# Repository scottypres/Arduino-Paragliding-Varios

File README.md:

# Arduino Paragliding Varios

GitHub: [`scottypres/Arduino-Paragliding-Varios`](https://github.com/scottypres/Arduino-Paragliding-Varios)
Local checkout: `~/Documents/GitHub/Vario_Adafruit_Featherwing` — the folder name predates the
rename and is *not* worth changing; git doesn't care what the working directory is called.

Two separate paragliding variometers live here. They share nothing but ideas — different
boards, different sketches, different PCBs. Each one keeps its firmware, KiCad projects and
notes inside its own top-level folder.

| | **SparkFun ESP32 WROOM Vario** | **Adafruit Feather Mini Vario** |
|---|---|---|
| Status | **Active.** All current work. | Older / on ice. |
| Board | SparkFun Thing Plus ESP32 WROOM-C | Adafruit ESP32 Feather V2 |
| Firmware | `Sparkfun ESP32 WROOM Vario/Arduino Scripts/Sparkfun_Vario/` (multi-file) | `Adafruit Feather Mini Vario/Arduino Scripts/oled_ssid_button_buzzer/` (single `.ino`) |
| FQBN | `esp32:esp32:esp32thing_plus_c` | `esp32:esp32:adafruit_feather_esp32_v2` |
| Battery sense | MAX17048 fuel gauge on I2C (21/22) | ADC on `BATT_MONITOR` |
| Last touched | ongoing | 2026-07-03 (`bdf2adf`) |

Sensors on both: BMP581 (pressure/altitude), SHT41 (temp/humidity), SH1106G OLED, piezo buzzers.
The SparkFun build adds GPS, an LSM6DSV16X IMU, SD logging and a web app.

---

## Where things are

```
Adafruit Feather Mini Vario/
  Arduino Scripts/oled_ssid_button_buzzer/   single-file firmware
  KiCAD Files/                               Buzzer PCB, Buzzer PCB with step up converter
  CAD Files/                                 3D models for the stack
  docs/

Sparkfun ESP32 WROOM Vario/
  Arduino Scripts/
    Sparkfun_Vario/          <-- THE firmware. Everything else is a side experiment.
    Sparkfun_Battery_Tester/ standalone battery-drain rig
    experiments/             a2dp beep latency, piezo tests, wifi manager/OTA spike
    iram_tests/              IRAM budget probes (why WiFi and BT can't ship together)
  KiCAD Files/               Buzzer PCB V2, Buzzer PCB V3 (rerouting traces)
  3D Printed Case/
  docs/                      SparkFun datasheets, SD-log backups, design specs
```

`Component References/` is duplicated under each variant's `KiCAD Files/` on purpose: KiCad
resolves 3D models via `${KIPRJMOD}/../Component References/...`, so each project needs its own
copy to open cleanly from its own folder.

**Not in git, safe to delete:** anything under a `.history/` folder (VS Code Local History),
`build/`, `build-wifi/`, `build-bt/`, `.pio/`. If you see a top-level `Arduino Scripts/` or
`KiCAD Files/` in your working copy, those are leftovers from before the per-board
restructure — they contain no source, only build and history junk.

---

## The two firmware builds (SparkFun)

Since v1.2.0 the WiFi build also carries **BLE vario telemetry** (NimBLE — small enough
to coexist with WiFi in IRAM; the old split existed because Bluedroid *Classic* wasn't).
The BT-only build remains as a no-WiFi variant. Selected in `radio_config.h`:

| Build | Radios | Gets you | Loses |
|---|---|---|---|
| **WiFi** (default) | WiFi + BLE | web app, OTA, WiFi portal, LK8EX1 telemetry to phone apps | — |
| **BT** | BLE only | LK8EX1 telemetry, lower power | web app, OTA |

IRAM is within ~2 KB of full on the combined build — `rgbLedWrite` is stubbed in
`power.cpp` to keep the RMT driver out; don't add libraries without watching the link.

```sh
cd "Sparkfun ESP32 WROOM Vario/Arduino Scripts/Sparkfun_Vario"

# WiFi image (default)
arduino-cli compile --fqbn esp32:esp32:esp32thing_plus_c --output-dir build-wifi .

# BT image
arduino-cli compile --fqbn esp32:esp32:esp32thing_plus_c --output-dir build-bt \
  --build-property compiler.cpp.extra_flags=-DVARIO_RADIO_BT .
```

Required libraries: `SparkFun MAX1704x Fuel Gauge Arduino Library`, `SparkFun 6DoF LSM6DSV16X`,
plus the usual Adafruit GFX/SH110X/SHT4x/BMP5xx, TinyGPSPlus, ESPAsyncWebServer, WiFiManager.

### Getting a build onto the device

1. **OTA** (WiFi image running): System tab → *Firmware update*, or
   `espota.py -i <ip> -p 3232 -a password -f build-wifi/Sparkfun_Vario.ino.bin`
   (hostname `sparkfun-vario`).
2. **SD self-flash** — the only way to reach the BT image. Copy both binaries to the SD card
   root as `/fw_wifi.bin` and `/fw_bt.bin`, then Menu → System → **Switch FW** flashes *the
   other* variant and reboots.
3. **USB** — `arduino-cli upload -p /dev/cu.usbserial-* --fqbn esp32:esp32:esp32thing_plus_c`.

---

## Firmware versions

`Sparkfun_Vario/version.h` holds a single `VARIO_FW_VERSION`. It is shown in three places:

- OLED: **Menu → System → About**
- Web app: the header (`SparkFun Vario v1.0.0-WiFi`) and System tab → *About*
- API: `GET /api/settings` → `fw_version`, `fw_radio`, `fw_build`

The radio suffix (`-WiFi` / `-BT`) is derived at compile time, so the version string always
says which of the two images is running. `fw_build` is `__DATE__ __TIME__`, which answers
"is the board running the build I just made?" without any build-time codegen.

**Bump `VARIO_FW_VERSION` and add a `CHANGELOG.md` line in the same commit that changes
behaviour.** Semver-ish: patch for fixes, minor for new menu items/features, major for
anything that breaks saved settings or the log format.

To check what a device is running:

```sh
curl -s http://172.20.10.2/api/settings | python3 -m json.tool | grep fw_
```

---

## Working on this repo

Development also happens in Claude Code **cloud** sessions that push straight to
`origin/main` (branch names like `worktree-bridge-cse_*`). **Always `git fetch` before you
start** — a local checkout has silently been 21 commits stale before, and flashing a stale
build erases features that only exist on the device.

Device is usually at `http://172.20.10.2/` on the iPhone-hotspot subnet (`172.20.10.x`).
It sleeps aggressively, so a failed curl means "asleep", not "broken".

`arduino_secrets.h` is gitignored; copy `arduino_secrets.example.h` if you need hardcoded
WiFi credentials. Normally the WiFi portal handles it instead.

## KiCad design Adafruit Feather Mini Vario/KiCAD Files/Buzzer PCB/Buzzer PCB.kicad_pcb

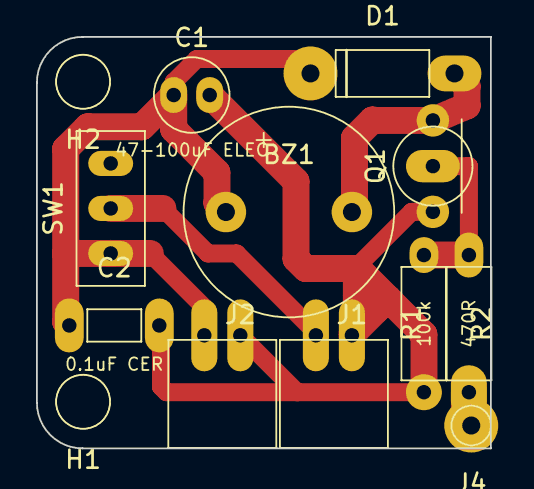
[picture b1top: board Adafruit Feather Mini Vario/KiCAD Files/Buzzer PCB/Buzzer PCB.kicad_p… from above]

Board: 2 copper layers, 25.2 x 22.9 mm, 13 parts (0 on the bottom side), 6 nets.

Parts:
BZ1: 12085 Passive Buzzer 42R; Buzzer_12x8.5mm_P7.62mm_Custom
C1: 47-100uF ELEC; CP_Radial_D5.0mm_P2.00mm
C2: 0.1uF CER; C_Disc_D3.0mm_W1.6mm_P2.50mm
D1: 1N5819; D_DO-41_SOD81_P10.16mm_Horizontal
H1, H2: NPTH_3.0mm; MountingHole_3.0mm
J1: JST-PH Battery IN; JST_PH_S2B-PH-K_1x02_P2.00mm_Horizontal
J2: JST-PH Feather BAT OUT; JST_PH_S2B-PH-K_1x02_P2.00mm_Horizontal
J4: Feather D13; PinHeader_1x01_P2.54mm_Vertical
Q1: S8050; TO-92_Inline_Wide_Formed
R1: 470R; R_Axial_DIN0207_L6.3mm_D2.5mm_P7.62mm_Horizontal
R2: 100k; R_Axial_DIN0207_L6.3mm_D2.5mm_P7.62mm_Horizontal
SW1: SS12D00G5; SS12D00G5_Custom

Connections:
BAT_IN: J1.1 (+), SW1.2 (COM)
BUZZER_BASE: Q1.2 (B), R1.2, R2.1
BUZZER_LOW: BZ1.2 (-), D1.2 (A), Q1.3 (C)
D13: J4.e (Feather D13), R1.1
GND: C1.2 (-), C2.2 (-), J1.2 (-), J2.2 (-), Q1.1 (E), R2.2
SW_BAT: BZ1.1 (+), C1.1 (+), C2.1 (+), D1.1 (K), J2.1 (+), SW1.1 (ON)

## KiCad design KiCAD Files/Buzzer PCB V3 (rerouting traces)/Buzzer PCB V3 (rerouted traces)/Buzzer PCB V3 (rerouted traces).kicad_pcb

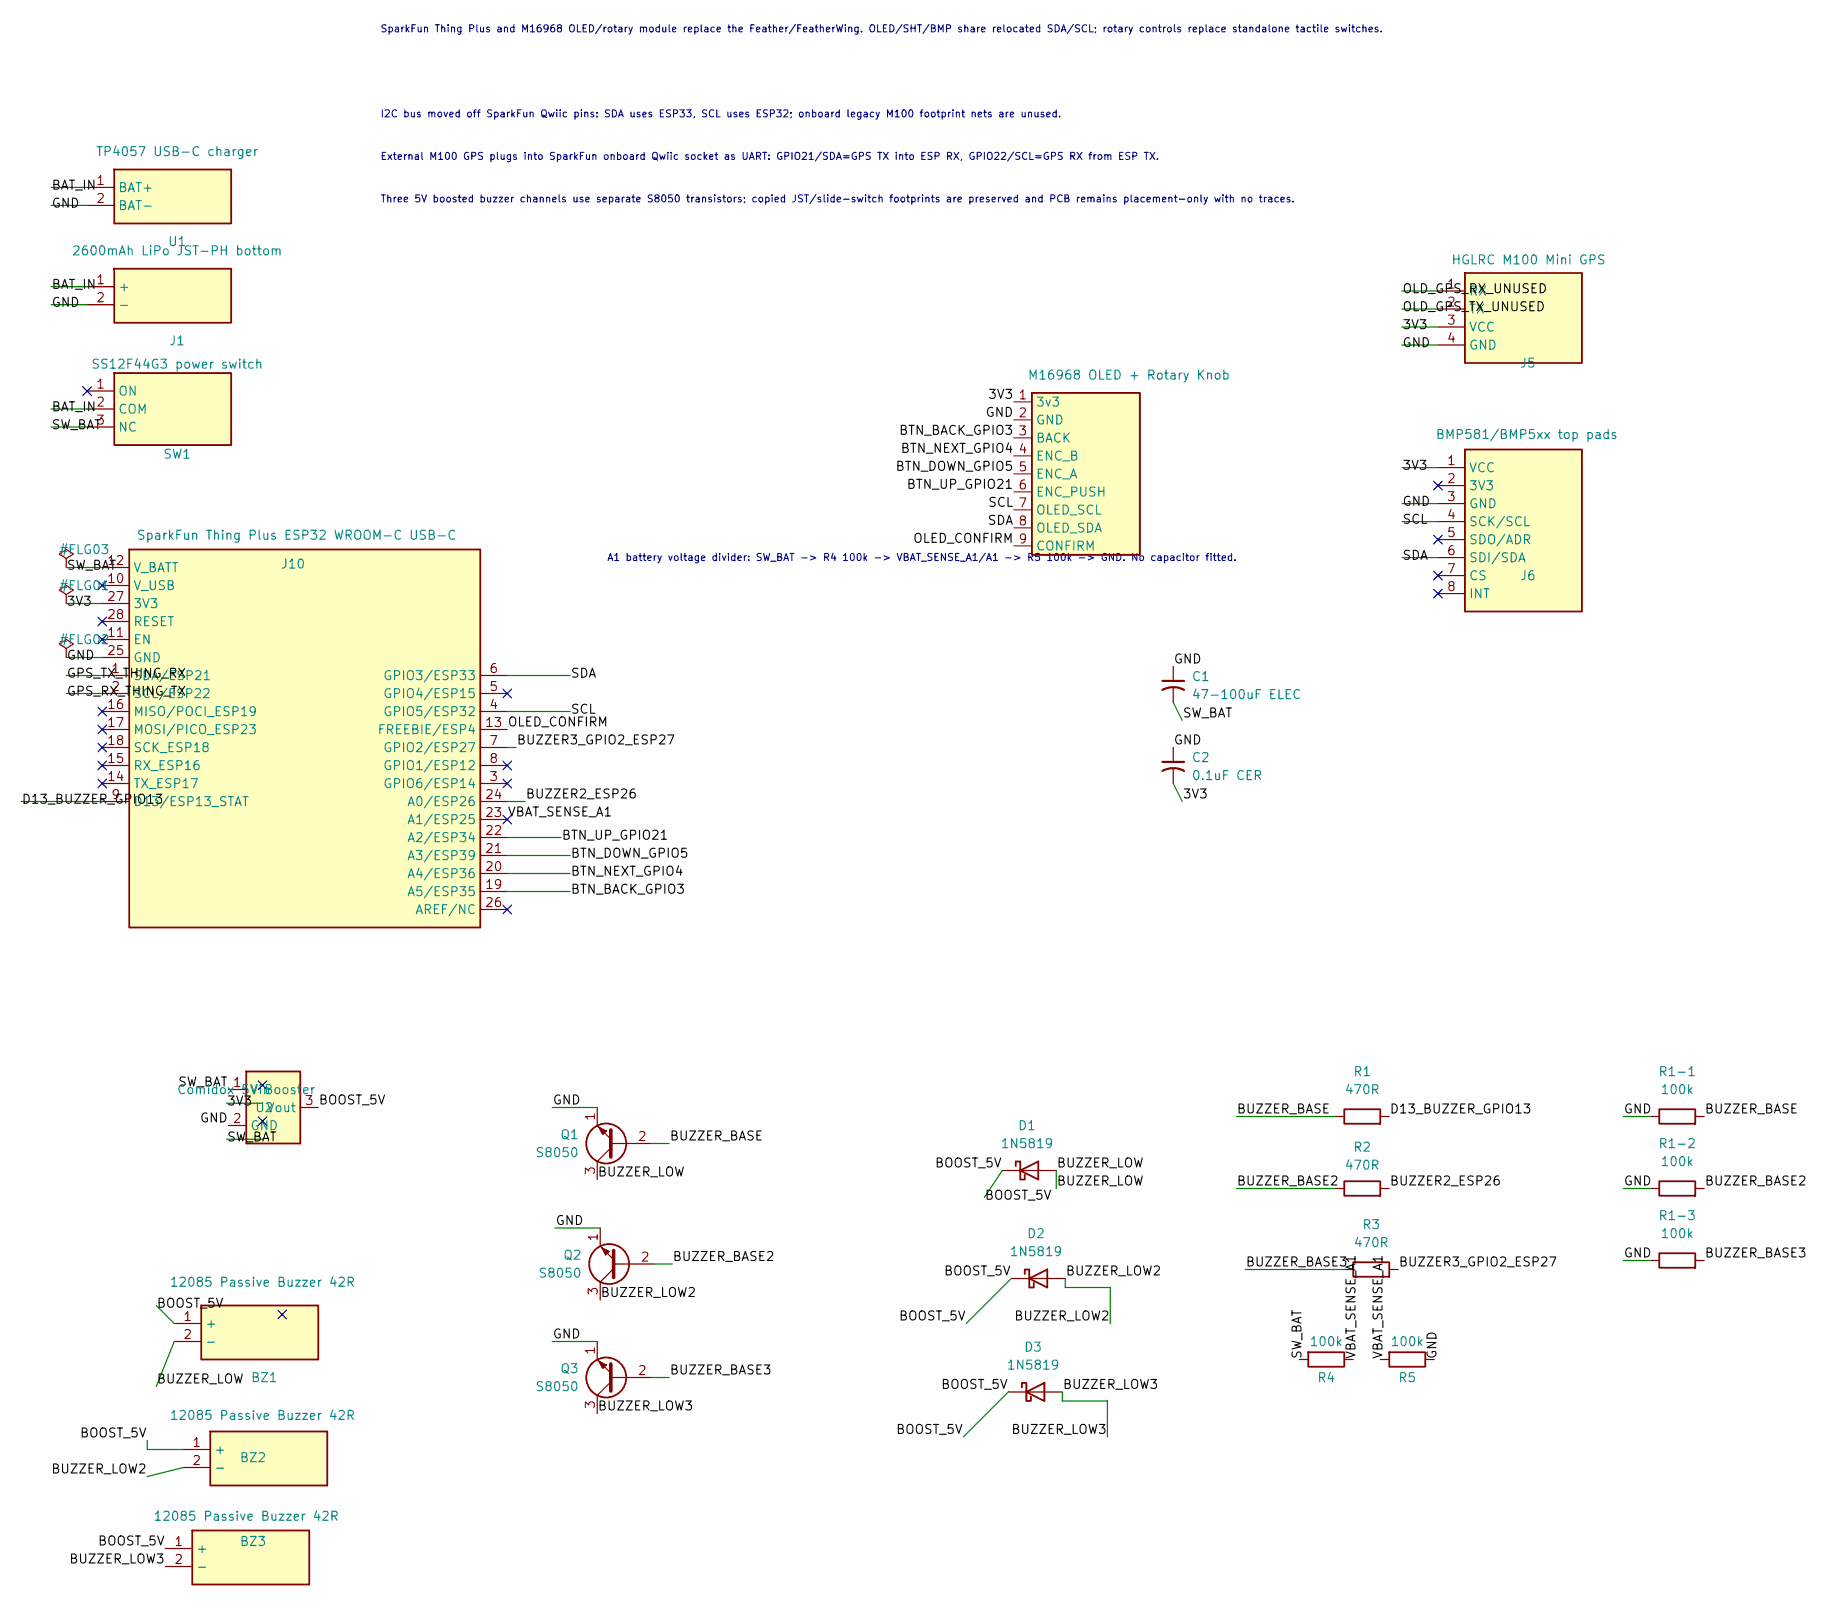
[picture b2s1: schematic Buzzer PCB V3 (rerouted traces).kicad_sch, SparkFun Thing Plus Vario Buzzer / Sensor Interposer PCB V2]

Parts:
BZ1, BZ2, BZ3: 12085 Passive Buzzer 42R; Buzzer_12x8.5mm_P7.62mm_Custom
C1: 47-100uF ELEC; CP_Radial_D5.0mm_P2.00mm
C2: 0.1uF CER; Ceramic_Cap_0.1uF_P5.00mm_V1
D1, D2, D3: 1N5819; D_DO-41_SOD81_P10.16mm_Horizontal
J1: 2600mAh LiPo JST-PH bottom; JST_PH_S2B-PH-K_1x02_P2.00mm_Horizontal
J5: HGLRC M100 Mini GPS; GPS_M100_15x15_4Pin_Back
J6: BMP581/BMP5xx top pads; Adafruit_BMP390_Breakout_Top
J10: SparkFun Thing Plus ESP32 WROOM-C USB-C; SparkFun_Thing_Plus_ESP32_WROOM_C_Header
J11: M16968 OLED + Rotary Knob; OLED_M16968_59x35_9Pin
Q1, Q2, Q3: S8050; TO-92_Inline
R1, R2, R3: 470R; R_Axial_DIN0207_L6.3mm_D2.5mm_P10.16mm_Horizontal
R1-1, R1-2, R1-3, R4, R5: 100k; R_Axial_DIN0207_L6.3mm_D2.5mm_P10.16mm_Horizontal
SW1: SS12F44G3 power switch; SS12F44G3_5.9x12.25_P3.00
U1: TP4057 USB-C charger; TP4057_Module_12.2x18.5
U2: Comidox 5V Booster; Comidox_5V_Booster_10.75x10.75_3Pin

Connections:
/3V3: C2.2, J5.3 (VCC), J6.1 (VCC), J10.27 (3V3), J11.1 (3v3)
/BAT_IN: J1.1 (+), SW1.2 (COM), U1.1 (BAT+)
/BOOST_5V: BZ1.1 (+), BZ2.1 (+), BZ3.1 (+), D1.1 (K), D2.1 (K), D3.1 (K), U2.3 (Vout)
/BTN_BACK_GPIO3: J10.19 (A5/ESP35), J11.3 (BACK)
/BTN_DOWN_GPIO5: J10.21 (A3/ESP39), J11.5 (ENC_A)
/BTN_NEXT_GPIO4: J10.20 (A4/ESP36), J11.4 (ENC_B)
/BTN_UP_GPIO21: J10.22 (A2/ESP34), J11.6 (ENC_PUSH)
/BUZZER2_ESP26: J10.24 (A0/ESP26), R2.2
/BUZZER3_GPIO2_ESP27: J10.7 (GPIO2/ESP27), R3.2
/BUZZER_BASE: Q1.2 (B), R1.1, R1-1.2
/BUZZER_BASE2: Q2.2 (B), R1-2.2, R2.1
/BUZZER_BASE3: Q3.2 (B), R1-3.2, R3.1
/BUZZER_LOW: BZ1.2 (-), D1.2 (A), Q1.3 (C)
/BUZZER_LOW2: BZ2.2 (-), D2.2 (A), Q2.3 (C)
/BUZZER_LOW3: BZ3.2 (-), D3.2 (A), Q3.3 (C)
/D13_BUZZER_GPIO13: J10.9 (D13/ESP13_STAT), R1.2
/GND: C1.1, C2.1, J1.2 (-), J5.4 (GND), J6.3 (GND), J10.25 (GND), J11.2 (GND), Q1.1 (E), Q2.1 (E), Q3.1 (E), R1-1.1, R1-2.1, R1-3.1, R5.1, U1.2 (BAT-), U2.2 (GND)
/GPS_RX_THING_TX: J10.2 (SCL/ESP22)
/GPS_TX_THING_RX: J10.1 (SDA/ESP21)
/OLD_GPS_RX_UNUSED: J5.1 (RX)
/OLD_GPS_TX_UNUSED: J5.2 (TX)
/OLED_CONFIRM: J10.13 (FREEBIE/ESP4), J11.9 (CONFIRM)
/SCL: J6.4 (SCK/SCL), J10.4 (GPIO5/ESP32), J11.7 (OLED_SCL)
/SDA: J6.6 (SDI/SDA), J10.6 (GPIO3/ESP33), J11.8 (OLED_SDA)
/SW_BAT: C1.2, J10.12 (V_BATT), R4.2, SW1.3 (NC), U2.1 (Vin)
/VBAT_SENSE_A1: J10.23 (A1/ESP25), R4.1, R5.2

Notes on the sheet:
External M100 GPS plugs into SparkFun onboard Qwiic socket as UART: GPIO21/SDA=GPS TX into ESP RX, GPIO22/SCL=GPS RX from ESP TX.
I2C bus moved off SparkFun Qwiic pins: SDA uses ESP33, SCL uses ESP32; onboard legacy M100 footprint nets are unused.
SparkFun Thing Plus and M16968 OLED/rotary module replace the Feather/FeatherWing. OLED/SHT/BMP share relocated SDA/SCL; rotary controls replace standalone tactile switches.
A1 battery voltage divider: SW_BAT -> R4 100k -> VBAT_SENSE_A1/A1 -> R5 100k -> GND. No capacitor fitted.
Three 5V boosted buzzer channels use separate S8050 transistors; copied JST/slide-switch footprints are preserved and PCB remains placement-only with no traces.

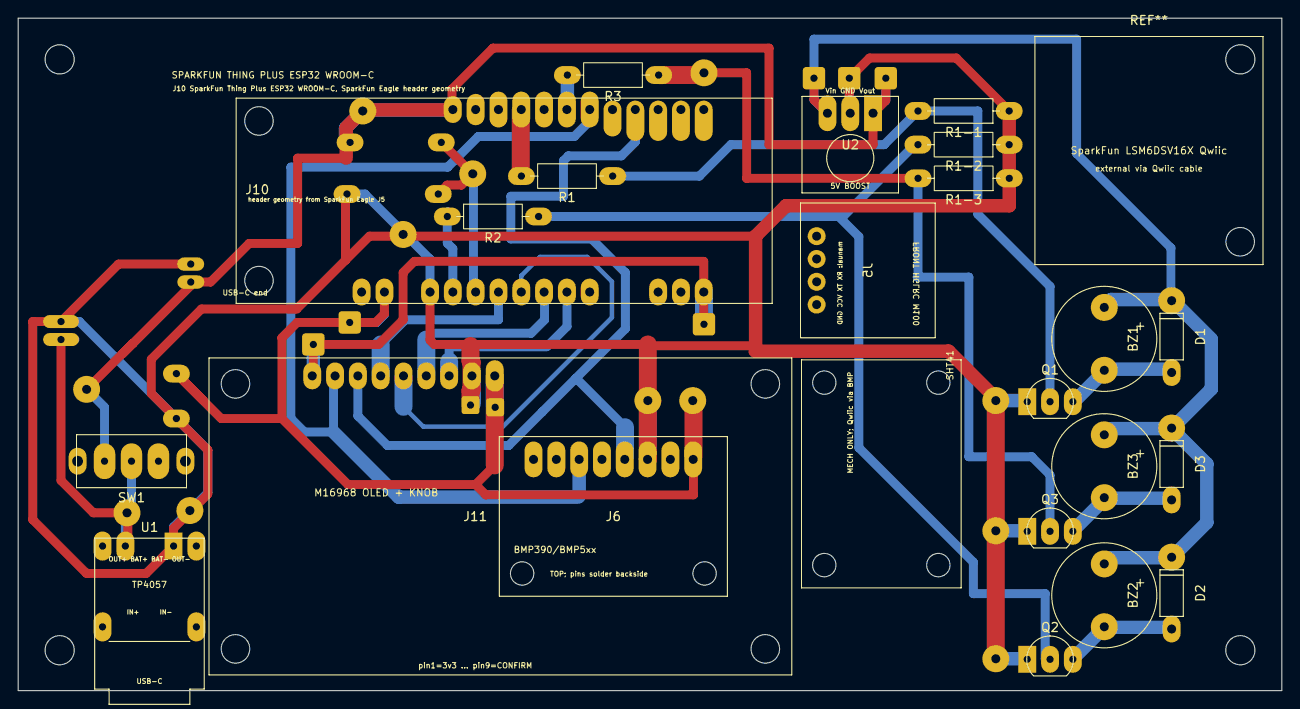
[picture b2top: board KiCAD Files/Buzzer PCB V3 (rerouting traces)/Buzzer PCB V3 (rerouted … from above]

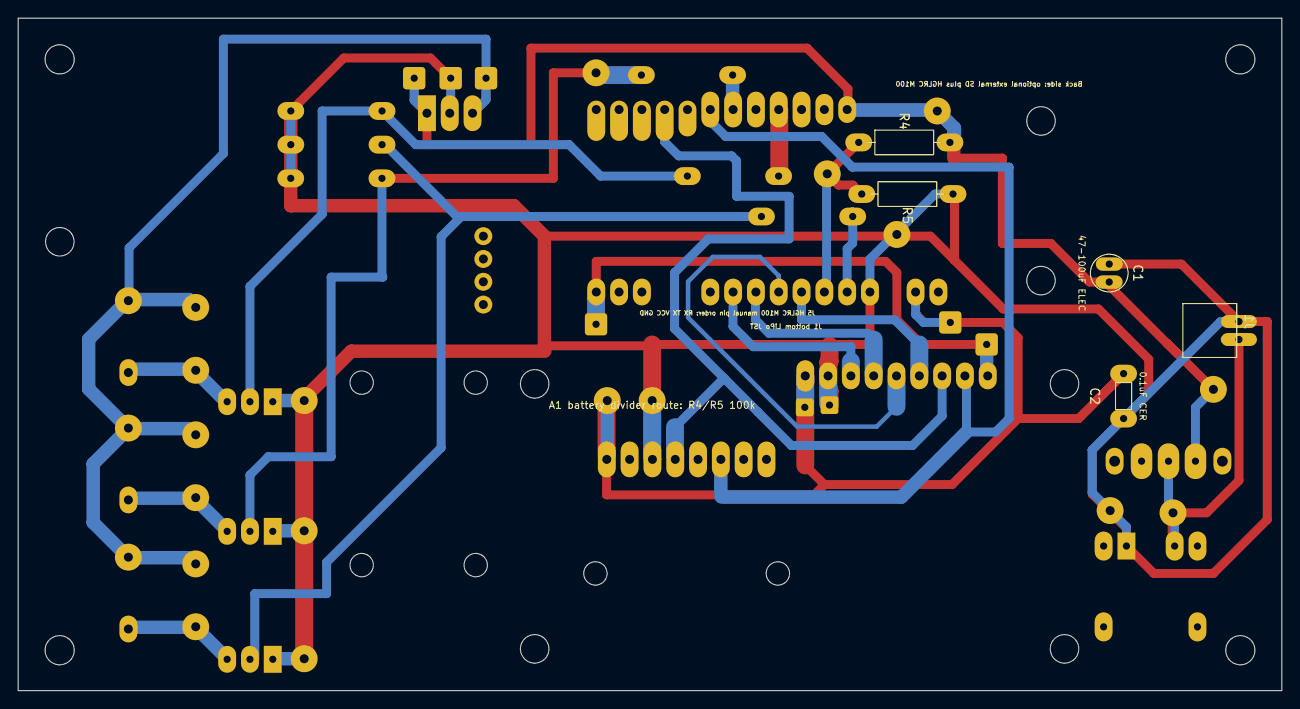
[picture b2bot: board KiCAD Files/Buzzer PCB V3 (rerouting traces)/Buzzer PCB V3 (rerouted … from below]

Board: 2 copper layers, 140.7 x 74.9 mm, 32 parts (5 on the bottom side), 22 nets.

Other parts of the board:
H1, H2, H3, H4: MountingHole_3.2mm_M3
J7: SHT41 mechanical only; Adafruit_SHT41_Breakout_Top

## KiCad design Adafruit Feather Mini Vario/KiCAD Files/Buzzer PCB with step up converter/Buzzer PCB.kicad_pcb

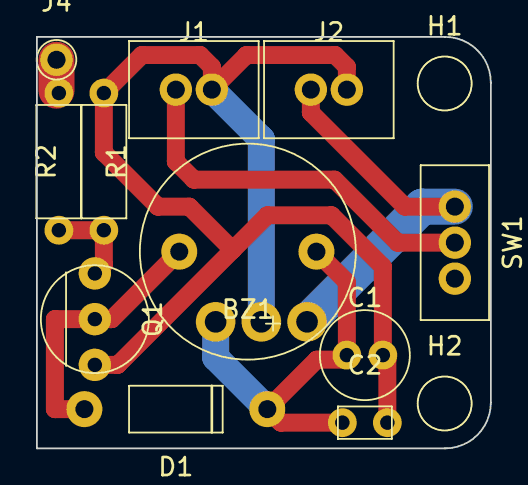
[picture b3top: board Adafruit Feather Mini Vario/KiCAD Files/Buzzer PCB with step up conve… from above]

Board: 2 copper layers, 25.2 x 22.9 mm, 14 parts (1 on the bottom side), 7 nets.

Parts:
BZ1: 12085 Passive Buzzer 42R; Buzzer_12x8.5mm_P7.62mm_Custom
C1: 47-100uF; CP_Radial_D5.0mm_P2.00mm
C2: 0.1uF; C_Disc_D3.0mm_W1.6mm_P2.50mm
D1: 1N5819; D_DO-41_SOD81_P10.16mm_Horizontal
H1, H2: NPTH_3.0mm; MountingHole_3.0mm
J1: JST-PH Battery IN; JST_PH_S2B-PH-K_1x02_P2.00mm_Horizontal
J2: JST-PH Feather BAT OUT; JST_PH_S2B-PH-K_1x02_P2.00mm_Horizontal
J3: Comidox Boost Module; Comidox_Boost_11x11_3Pin_Custom
J4: Feather D13; PinHeader_1x01_P2.54mm_Vertical
Q1: S8050; TO-92_Inline_Wide_Formed
R1: 470R; R_Axial_DIN0207_L6.3mm_D2.5mm_P7.62mm_Horizontal
R2: 100k; R_Axial_DIN0207_L6.3mm_D2.5mm_P7.62mm_Horizontal
SW1: SS12D00G5; SS12D00G5_Custom

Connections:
BAT_IN: J1.1 (+), SW1.2 (COM)
BOOST_5V: BZ1.1 (+), C1.1 (+), C2.1 (+), D1.1 (K), J3.3 (VOUT)
BUZZER_BASE: Q1.1 (B), R1.2, R2.1
BUZZER_LOW: BZ1.2 (-), D1.2 (A), Q1.2 (C)
D13: J4.1 (Feather D13), R1.1
GND: C1.2 (-), C2.2 (-), J1.2 (-), J2.2 (-), J3.2 (GND), Q1.3 (E), R2.2
SW_BAT: J2.1 (+), J3.1 (VIN), SW1.1 (ON)

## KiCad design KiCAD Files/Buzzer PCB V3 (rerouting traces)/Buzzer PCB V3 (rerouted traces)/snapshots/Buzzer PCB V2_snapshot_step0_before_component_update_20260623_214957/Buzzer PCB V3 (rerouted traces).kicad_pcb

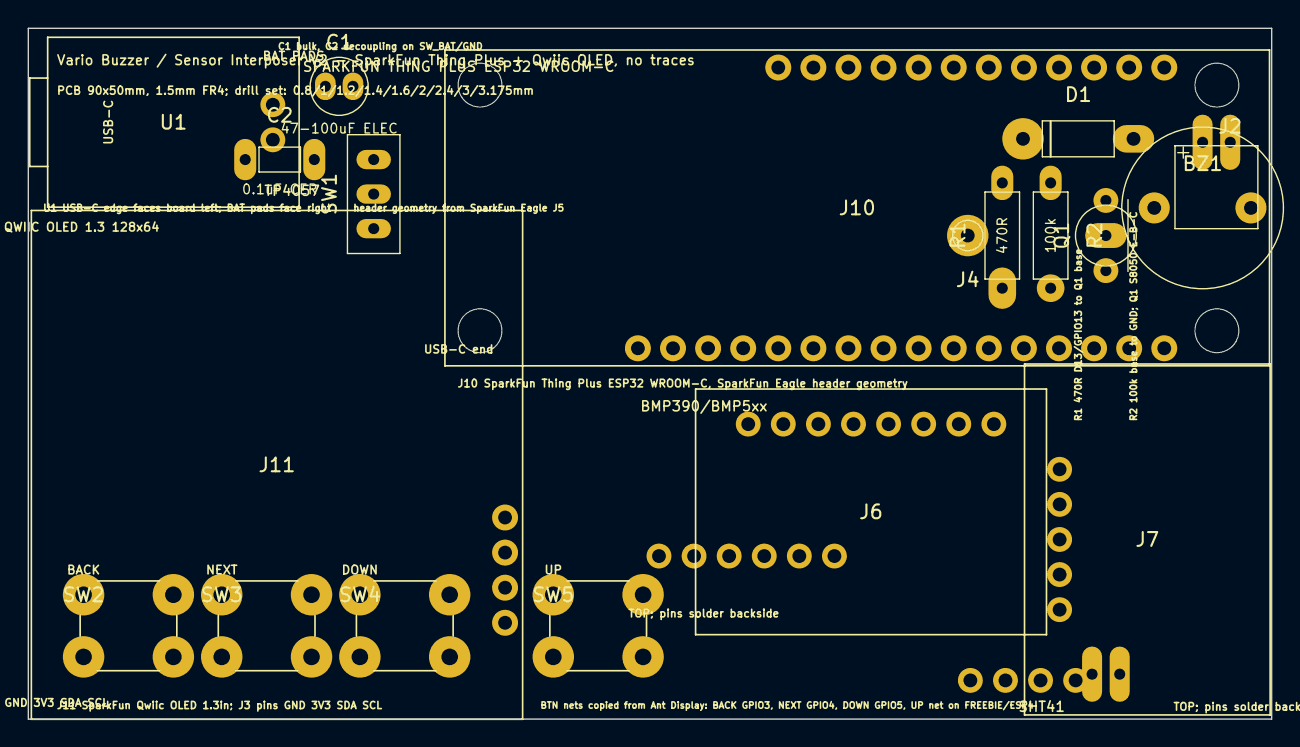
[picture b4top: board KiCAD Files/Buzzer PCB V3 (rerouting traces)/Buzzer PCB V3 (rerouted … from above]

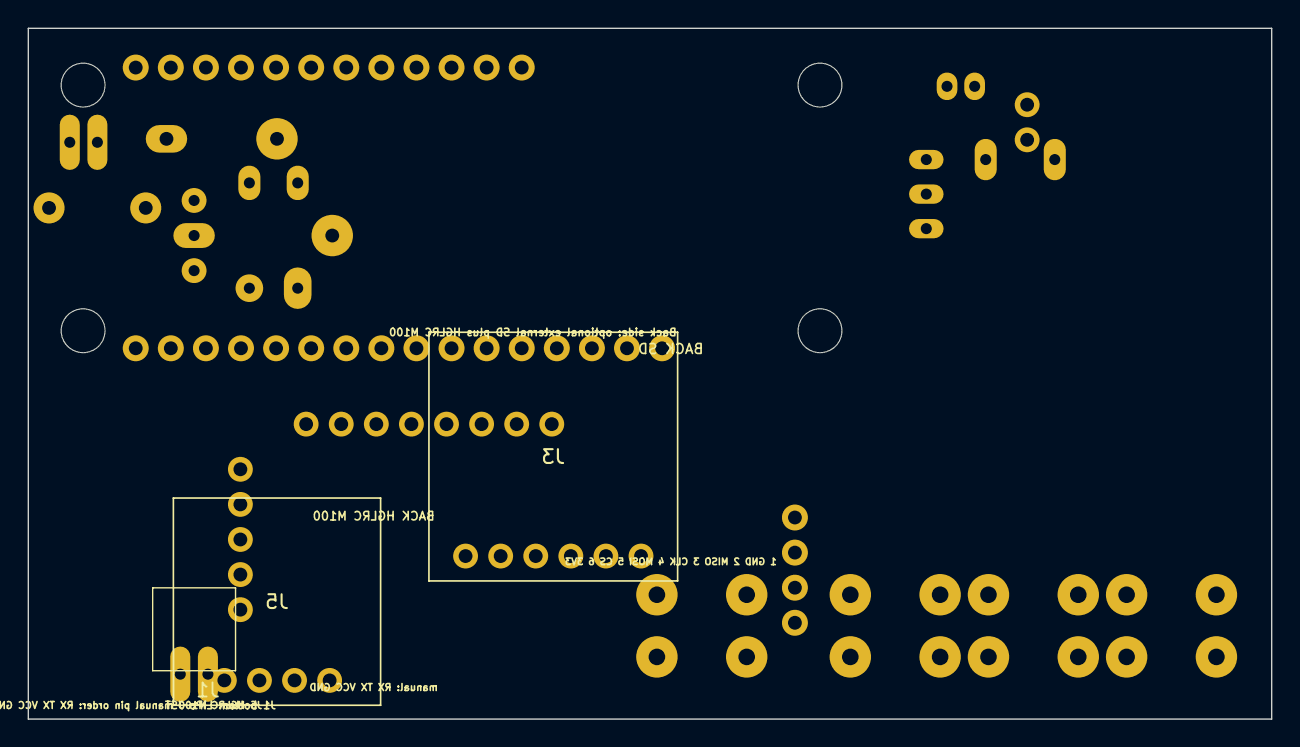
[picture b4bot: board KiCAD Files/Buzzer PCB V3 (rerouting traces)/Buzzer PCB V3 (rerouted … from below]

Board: 2 copper layers, 90.0 x 50.0 mm, 22 parts (3 on the bottom side), 19 nets, no tracks yet.

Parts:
BZ1: 12085 Passive Buzzer 42R; Buzzer_12x8.5mm_P7.62mm_Custom
C1: 47-100uF ELEC; CP_Radial_D5.0mm_P2.00mm
C2: 0.1uF CER; C_Disc_D3.0mm_W1.6mm_P2.50mm
D1: 1N5819; D_DO-41_SOD81_P10.16mm_Horizontal
J1: 2600mAh LiPo JST-PH bottom; JST_PH_S2B-PH-K_1x02_P2.00mm_Horizontal
J2: Legacy SW_BAT/GND out; JST_PH_S2B-PH-K_1x02_P2.00mm_Horizontal
J3: Optional external SD module; Thing Plus has onboa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; SD_Module_18x18_6Pin_Back
J4: Legacy D13 test pad; PinHeader_1x01_P2.54mm_Vertical
J5: HGLRC M100 Mini GPS manual pinout; GPS_M100_15x15_4Pin_Back
J6: BMP390/BMP5xx top pads; Adafruit_BMP390_Breakout_Top
J7: SHT41 top pads; Adafruit_SHT41_Breakout_Top
J10: SparkFun Thing Plus ESP32 WROOM-C USB-C header; SparkFun_Thing_Plus_ESP32_WROOM_C_Header
J11: SparkFun Qwiic OLED 1.3in module; SparkFun_Qwiic_OLED_1p3_Module
Q1: S8050; TO-92_Inline_Wide_Formed
R1: 470R; R_Axial_DIN0207_L6.3mm_D2.5mm_P7.62mm_Horizontal
R2: 100k; R_Axial_DIN0207_L6.3mm_D2.5mm_P7.62mm_Horizontal
SW1: SS12D00G5; SS12D00G5_Custom
SW2: BACK; Ant_Display_SW_PUSH_6mm_H5mm
SW3: NEXT; Ant_Display_SW_PUSH_6mm_H5mm
SW4: DOWN; Ant_Display_SW_PUSH_6mm_H5mm
SW5: UP; Ant_Display_SW_PUSH_6mm_H5mm
U1: TP4057 USB-C charger; TP4057_Module_18.2x12.3

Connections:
3V3: J3.6 (3V3), J5.3 (VCC 3.3-5V), J6.1 (VCC), J6.2 (3V3), J7.1 (VCC), J7.2 (3V3), J10.27 (3V3), J11.2 (VDD)
BAT_IN: J1.1 (+), SW1.2 (COM), U1.1 (BAT+)
BTN_BACK_GPIO3: J10.6 (GPIO3 / ESP33), SW2.1
BTN_DOWN_GPIO5: J10.4 (GPIO5 / ESP32), SW4.1
BTN_NEXT_GPIO4: J10.5 (GPIO4 / ESP15), SW3.1
BTN_UP_GPIO21: J10.13 (FREEBIE / ESP4), SW5.1
BUZZER_BASE: Q1.2 (B), R1.2, R2.1
BUZZER_LOW: BZ1.2 (-), D1.2 (A), Q1.3 (C)
D13_BUZZER_GPIO13: J4.e (D13/GPIO13 test), J10.9 (GPIO0 / ESP13 / STAT), R1.1
GND: C1.2 (-), C2.2 (-), J1.2 (-), J2.2 (-), J3.1 (GND), J5.4 (GND), J6.3 (GND), J7.3 (GND), J10.25 (GND), J11.1 (GND), Q1.1 (E), R2.2, SW2.2, SW3.2, SW4.2, SW5.2, U1.2 (BAT-)
GPS_RX_THING_TX: J5.1 (RX), J10.14 (TX / ESP17)
GPS_TX_THING_RX: J5.2 (TX), J10.15 (RX / ESP16)
SCL: J6.4 (SCK/SCL), J7.4 (SCL), J10.2 (SCL / ESP22), J11.4 (SCL)
SDA: J6.6 (SDI/SDA), J7.5 (SDA), J10.1 (SDA / ESP21), J11.3 (SDA)
SD_CS_GPIO2: J3.5 (CS), J10.7 (GPIO2 / ESP27)
SPI_MISO: J3.2 (MISO), J10.16 (POCI / ESP19)
SPI_MOSI: J3.4 (MOSI), J10.17 (PICO / ESP23)
SPI_SCK: J3.3 (CLK), J10.18 (SCK / ESP18)
SW_BAT: BZ1.1 (+), C1.1 (+), C2.1 (+), D1.1 (K), J2.1 (+), J10.12 (V_BATT), SW1.1 (ON)

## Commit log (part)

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2026-06-20 Rev 1
2026-06-20 wiki ingest
2026-06-21 FlatCAM ready
2026-06-21 done
2026-06-21 CAM ready
2026-06-21 deleted adafruit cad parts
2026-06-21 V2 PCB done
2026-06-22 two_sided
2026-06-22 backside full clear
2026-06-22 buzzer
2026-06-22 Fix S8050 pinout and buzzer test interval
2026-06-22 Fixed transistor pins
2026-06-22 pins_fixed
2026-06-22 Add Buzzer PCB V2 KiCad project
2026-06-23 V2 with sparkfun
2026-06-23 Traces
2026-06-23 Add persisted module defaults and WiFi setup portal
2026-06-23 Delay vario audio until BMP warmup
2026-06-23 Defer WiFi until after BMP warmup
2026-06-23 Persist altitude zero across resets
2026-06-23 Add web settings UI and WiFi reset menu
2026-06-23 Show sketch memory in menu and web UI
2026-06-23 Add temperature compensation TODO
2026-06-23 Add startup beep and volume settings
2026-06-23 Remove NeoPixel controls
2026-06-23 Fix WiFi reset and menu responsiveness
2026-06-23 Fallback to BMP temperature when SHT unavailable
2026-06-23 Remove hardcoded WiFi fallback
2026-06-23 Improve OLED menu button responsiveness
2026-06-23 Fix setup AP crash during WiFi reset
2026-06-23 Make setup AP open
2026-06-23 Updated Component References for Buzzer PCB V2
2026-06-24 Before component update: OLED/SD/TP4057 footprint swap, remove SW2-SW5, add booster + BZ2/BZ3 buzzer drivers
    KiCad-MCP-Checkpoint: true
    Project-Path: KiCAD Files/Buzzer PCB V2
2026-06-24 Restore KiCad component references and footprints
2026-06-24 Reposition buzzer PCB footprints and add SHT41 header
2026-06-25 updated pcb
2026-06-25 final routing
2026-06-25 Latest board
2026-06-25 getting close
2026-06-25 about to change GPS pins
2026-06-26 ready to mill
2026-06-26 BACK NPTH 3.175mm
2026-06-26 DEEP CORNER HOLES
2026-06-26 last attempt
2026-06-26 final attempt
2026-06-26 final_attempt
2026-06-26 last attemp
2026-06-26 REATTEMPT
2026-06-26 Add SparkFun vario Arduino sketch
2026-06-26 Use SH1106 OLED and local WiFi secrets
2026-06-27 Add WiFi setup portal for SparkFun vario
2026-06-27 Save V3 KiCad board before manual via DRC modeling
2026-06-27 FInal Sparkfun Version
2026-06-27 final
2026-06-28 fixed 2mm isolation
2026-06-28 FIX MISSING TRACES
2026-06-28 fixed with 0.4mm isolation
2026-06-28 Add Feather battery logging controls
